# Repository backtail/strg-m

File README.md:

# ctrl+m
3HP Eurorack module
CV modifier

### Render

### Pots
- **Offset**: offesets, full range -5V to 5V
- **Range**: attenuates and/or amplifies, full range gain 0 to 1.2
- **Clip**: clips from +-6V to +-10V

### LEDs
- upper LED shows current voltage in the Range of 0V to 5V
- lower LED shows current voltage in the Range of -5V to 0V

## Footprints Libraries
Use provided submodule folder to link footprints locally in the project
- OS_Connectors
- OS_Scribbles

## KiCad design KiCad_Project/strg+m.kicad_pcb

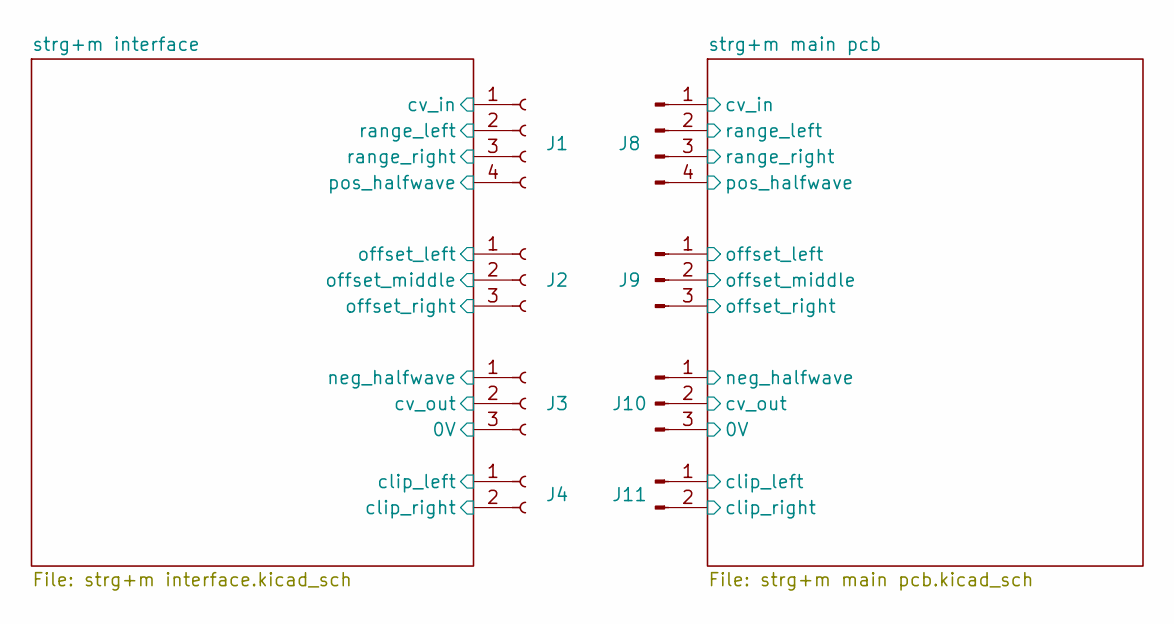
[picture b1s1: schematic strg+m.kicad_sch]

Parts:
J1: Conn_01x04_Female; PinHeader_1x04_P2.54mm_Vertical
J2, J3: Conn_01x03_Female; PinHeader_1x03_P2.54mm_Vertical
J4: Conn_01x02_Female; PinHeader_1x02_P2.54mm_Vertical
J8: Conn_01x04_Male; PinSocket_1x04_P2.54mm_Vertical
J9, J10: Conn_01x03_Male; PinSocket_1x03_P2.54mm_Vertical
J11: Conn_01x02_Male; PinSocket_1x02_P2.54mm_Vertical

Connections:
/strg+m interface/0V: J3.3; also elsewhere on the board
/strg+m interface/clip_left: J4.1; also elsewhere on the board
/strg+m interface/clip_right: J4.2; also elsewhere on the board
/strg+m interface/cv_in: J1.1; also elsewhere on the board
/strg+m interface/cv_out: J3.2; also elsewhere on the board
/strg+m interface/neg_halfwave: J3.1; also elsewhere on the board
/strg+m interface/offset_left: J2.1; also elsewhere on the board
/strg+m interface/offset_middle: J2.2; also elsewhere on the board
/strg+m interface/offset_right: J2.3; also elsewhere on the board
/strg+m interface/pos_halfwave: J1.4; also elsewhere on the board
/strg+m interface/range_left: J1.2; also elsewhere on the board
/strg+m interface/range_right: J1.3; also elsewhere on the board
/strg+m main pcb/clip_left: J8.3, J11.1; also elsewhere on the board
/strg+m main pcb/clip_right: J11.2; also elsewhere on the board
/strg+m main pcb/cv_in: J8.1; also elsewhere on the board
/strg+m main pcb/cv_out: J10.2; also elsewhere on the board
/strg+m main pcb/neg_halfwave: J10.1; also elsewhere on the board
/strg+m main pcb/offset_left: J9.1; also elsewhere on the board
/strg+m main pcb/offset_middle: J9.2; also elsewhere on the board
/strg+m main pcb/offset_right: J9.3; also elsewhere on the board
/strg+m main pcb/pos_halfwave: J8.4; also elsewhere on the board
/strg+m main pcb/range_left: J8.2; also elsewhere on the board
GND: J10.3; also elsewhere on the board

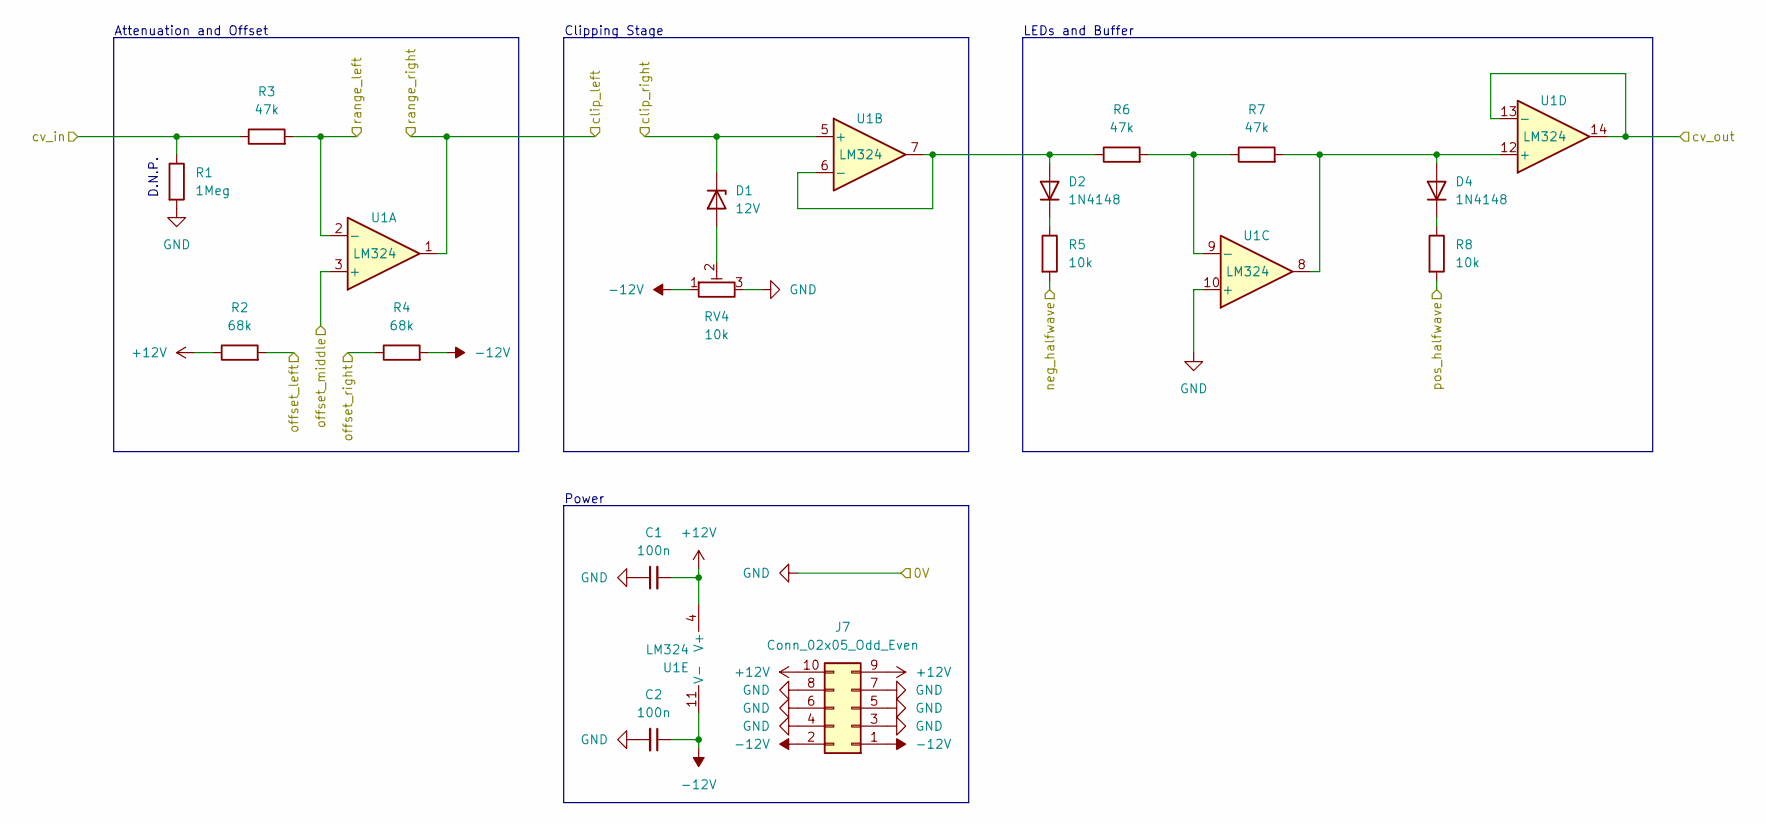
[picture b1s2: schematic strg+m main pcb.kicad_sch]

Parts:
C1, C2: 100n; C_1206_3216Metric
D1: 12V; D_1206_3216Metric
D2, D4: 1N4148; D_1206_3216Metric
J7: Conn_02x05_Odd_Even; IDC-Header_2x05_P2.54mm_Vertical
R1: 1Meg; R_1206_3216Metric
R2, R4: 68k; R_1206_3216Metric
R3, R6, R7: 47k; R_1206_3216Metric
R5, R8: 10k; R_1206_3216Metric
RV4: 10k; Potentiometer_Bourns_TC33X_Vertical
U1: LM324; SOIC-14_3.9x8.7mm_P1.27mm

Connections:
+12V: C1.2, J7.9, J7.10, R2.1, U1.4 (V+)
-12V: C2.1, J7.1, J7.2, R4.2, RV4.1, U1.11 (V-)
/strg+m main pcb/clip_left: U1.1; also elsewhere on the board
/strg+m main pcb/clip_right: D1.1 (K), U1.5 (+); also elsewhere on the board
/strg+m main pcb/cv_in: R1.1, R3.1; also elsewhere on the board
/strg+m main pcb/cv_out: U1.13 (-), U1.14; also elsewhere on the board
/strg+m main pcb/neg_halfwave: R5.2; also elsewhere on the board
/strg+m main pcb/offset_left: R2.2; also elsewhere on the board
/strg+m main pcb/offset_middle: U1.3 (+); also elsewhere on the board
/strg+m main pcb/offset_right: R4.1; also elsewhere on the board
/strg+m main pcb/pos_halfwave: R8.2; also elsewhere on the board
/strg+m main pcb/range_left: R3.2, U1.2 (-); also elsewhere on the board
GND: C1.1, C2.2, J7.3, J7.4, J7.5, J7.6, J7.7, J7.8, R1.2, RV4.3, U1.10 (+); also elsewhere on the board
unnamed: D1.2 (A), RV4.2
unnamed: D2.1 (K), R5.1
unnamed: D2.2 (A), R6.1, U1.6 (-), U1.7
unnamed: D4.1 (K), R8.1
unnamed: D4.2 (A), R7.2, U1.8, U1.12 (+)
unnamed: R6.2, R7.1, U1.9 (-)

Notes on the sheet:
Power
D.N.P.
Attenuation and Offset
Clipping Stage
LEDs and Buffer

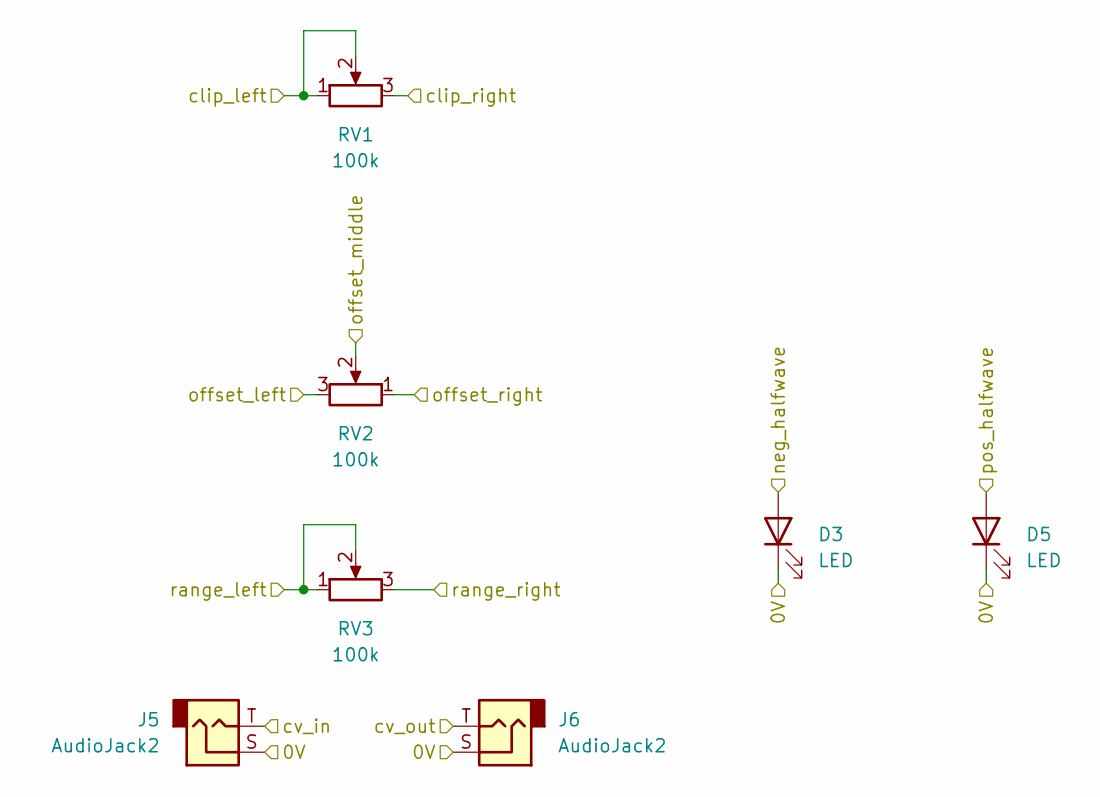
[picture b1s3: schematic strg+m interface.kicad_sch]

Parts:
D3, D5: LED; LED_D3.0mm
J5, J6: AudioJack2; PJ-392
RV1, RV2, RV3: 100k; Potentiometer_Alps_RK09K_Single_Vertical

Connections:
/strg+m interface/0V: D3.1 (K), D5.1 (K), J5.S, J6.S; also elsewhere on the board
/strg+m interface/clip_left: RV1.1, RV1.2; also elsewhere on the board
/strg+m interface/clip_right: RV1.3; also elsewhere on the board
/strg+m interface/cv_in: J5.T; also elsewhere on the board
/strg+m interface/cv_out: J6.T; also elsewhere on the board
/strg+m interface/neg_halfwave: D3.2 (A); also elsewhere on the board
/strg+m interface/offset_left: RV2.3; also elsewhere on the board
/strg+m interface/offset_middle: RV2.2; also elsewhere on the board
/strg+m interface/offset_right: RV2.1; also elsewhere on the board
/strg+m interface/pos_halfwave: D5.2 (A); also elsewhere on the board
/strg+m interface/range_left: RV3.1, RV3.2; also elsewhere on the board
/strg+m interface/range_right: RV3.3; also elsewhere on the board

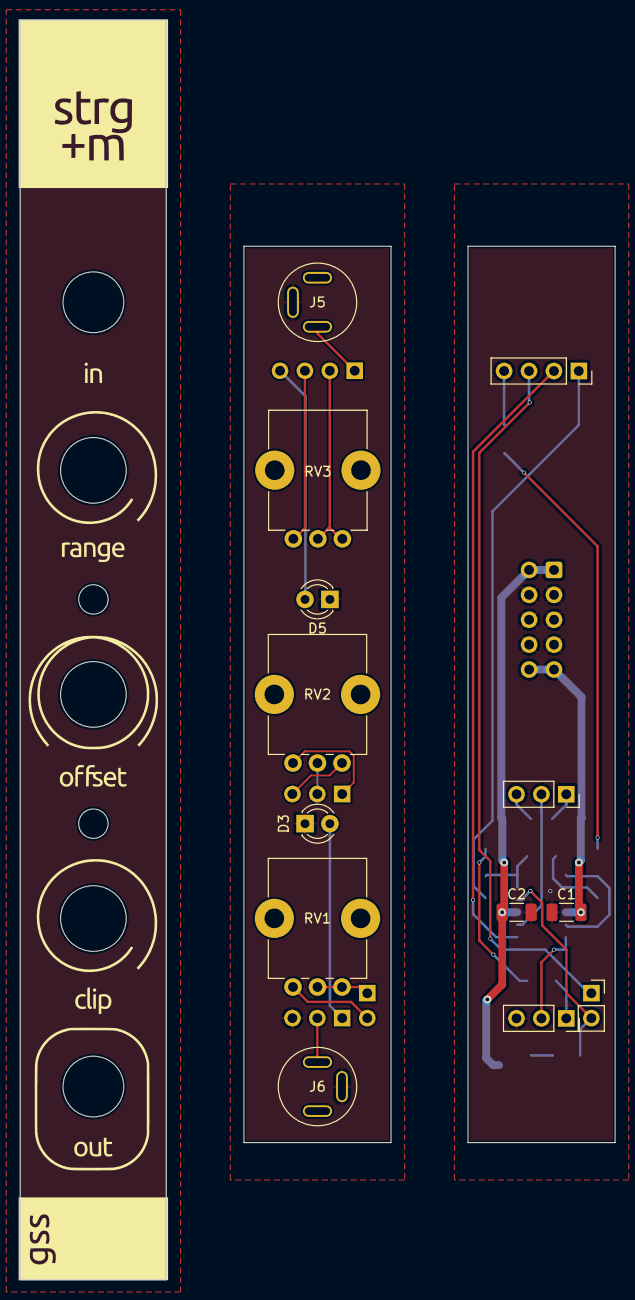
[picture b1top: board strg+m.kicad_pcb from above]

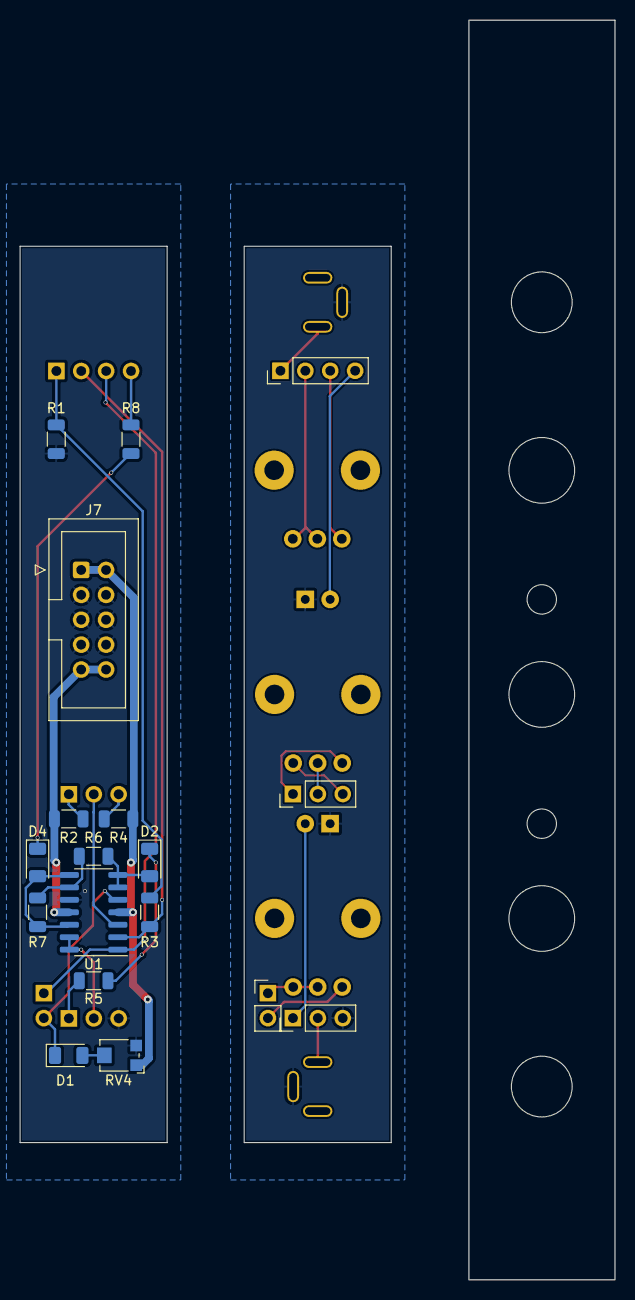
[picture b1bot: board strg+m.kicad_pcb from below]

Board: 2 copper layers, 60.7 x 128.5 mm, 31 parts (18 on the bottom side), 31 nets.

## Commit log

2022-02-22 initial commit / add readme
2022-02-22 add standard .gitignore
2022-02-22 add LTSpice Simulation
2022-02-22 add KiCad Project
2022-02-22 add KiCad Schematic
2022-02-22 add KiCad PCB Layout
2022-02-22 add frontpanel design
2022-02-22 add KiCad frontpanel footprint
2022-02-22 add KiCad footprint library submodule
2022-02-22 add frontpanel design to readme
2022-02-22 add Footprint Library submodule
2022-02-22 add new footprints
2022-02-22 add fronplate to pcb layout
2022-02-22 add custom 3d models
2022-03-15 update gitignore
2022-03-15 update render
2022-03-15 remove frontpanel png
2022-03-15 add BOM
2022-03-15 update schematic
2022-03-15 update pcb layout
2024-10-23 add old commits
